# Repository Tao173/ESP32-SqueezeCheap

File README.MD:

This was my first attempt at making a cheap squeeze client for multi room audio using 
https://github.com/sle118/squeezelite-esp32
I used the ESP32-A1S to avoid having to solder too many SMD parts. 
This was a mistake as the A1S is a massive pain to work with. 
This board also has a fair amount of digital noise and I'm too inexperienced to determine if its the board design or the A1S. 

I suggest you do not use this version and use my next revision.

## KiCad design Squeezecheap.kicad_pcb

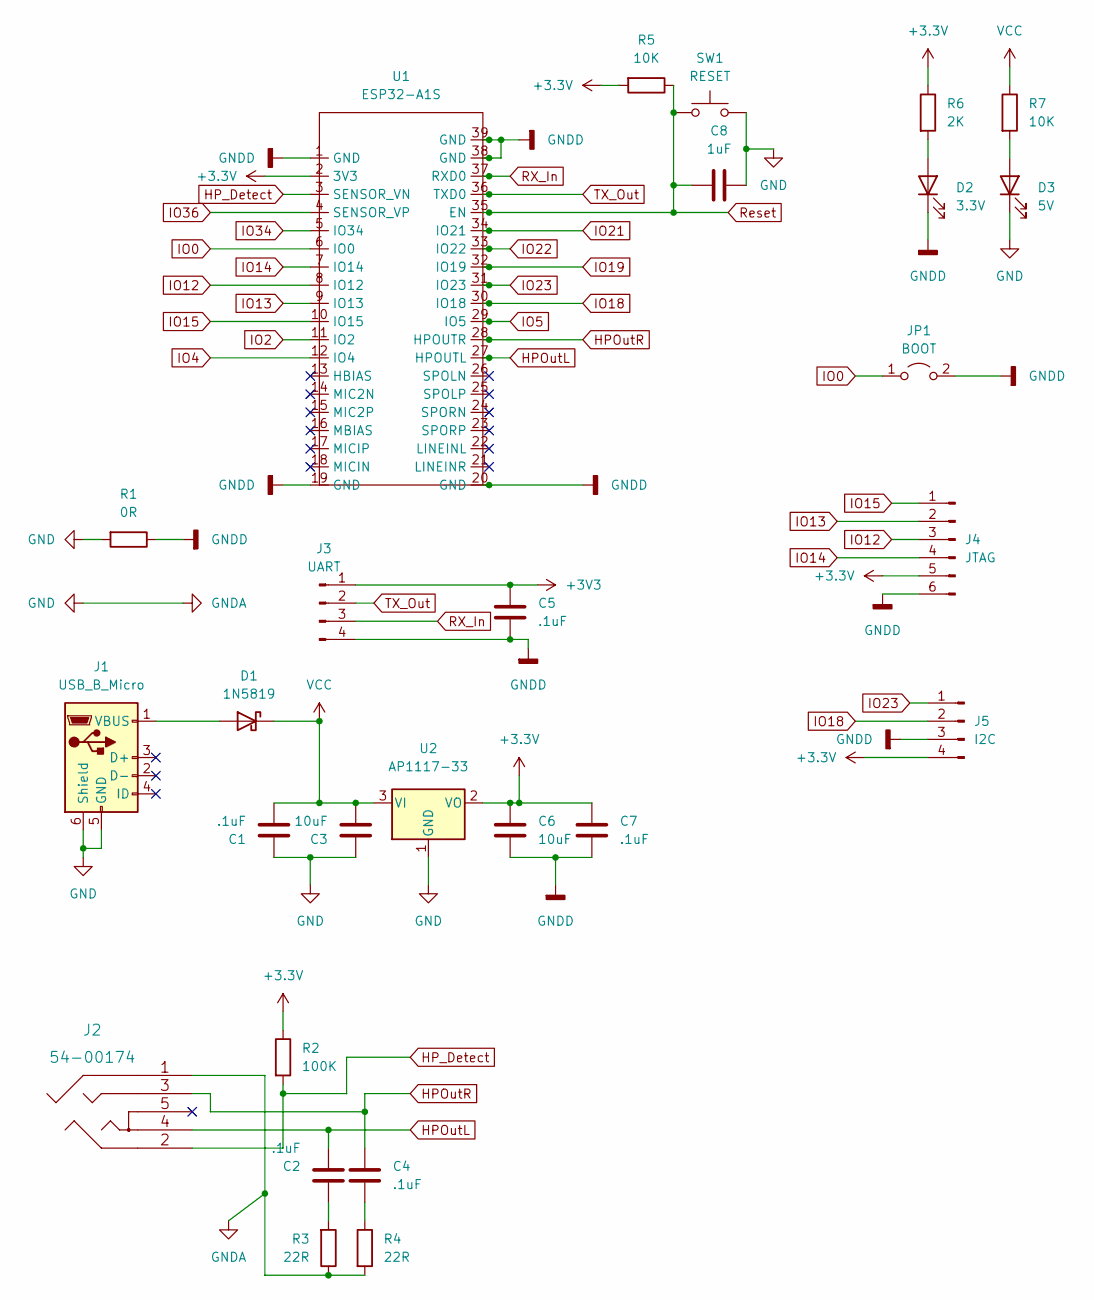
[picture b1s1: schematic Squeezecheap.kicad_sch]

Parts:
C1, C2, C4, C5, C7: .1uF; C_0805_2012Metric_Pad1.18x1.45mm_HandSolder
C3, C6: 10uF; C_0805_2012Metric_Pad1.18x1.45mm_HandSolder
C8: 1uF; C_0805_2012Metric_Pad1.18x1.45mm_HandSolder
D1: 1N5819; D_0805_2012Metric_Pad1.15x1.40mm_HandSolder
D2: 3.3V; LED_0805_2012Metric_Pad1.15x1.40mm_HandSolder
D3: 5V; LED_0805_2012Metric_Pad1.15x1.40mm_HandSolder
J1: USB_B_Micro; USB_Micro-B_Amphenol_10118194_Horizontal
J2: 54-00174
J3: UART; PinHeader_1x04_P2.54mm_Vertical
J4: JTAG; PinHeader_1x06_P2.54mm_Vertical
J5: I2C; PinHeader_1x04_P2.54mm_Vertical
JP1: BOOT; SolderJumper-2_P1.3mm_Open_Pad1.0x1.5mm
R1: 0R; R_0805_2012Metric_Pad1.20x1.40mm_HandSolder
R2: 100K; R_0805_2012Metric_Pad1.20x1.40mm_HandSolder
R3, R4: 22R; R_0805_2012Metric_Pad1.20x1.40mm_HandSolder
R5, R7: 10K; R_0805_2012Metric_Pad1.20x1.40mm_HandSolder
R6: 2K; R_0805_2012Metric_Pad1.20x1.40mm_HandSolder
SW1: RESET; SW_SPST_B3U-1000P
U1: ESP32-A1S
U2: AP1117-33; SOT-223-3_TabPin2

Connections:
GND: C1.1, C3.1, C8.1, D3.1 (K), J1.5 (GND), J1.6 (Shield), J2.1, R1.2, R3.1, R4.2, SW1.2, U2.1 (GND)
GNDD: C5.2, C6.2, C7.2, D2.1 (K), J3.4, J4.6, J5.3, JP1.2 (B), R1.1, U1.1 (GND), U1.19 (GND), U1.20 (GND), U1.38 (GND), U1.39 (GND)
HPOutL: C2.2, J2.4, U1.27 (HPOUTL)
HPOutR: C4.1, J2.3, U1.28 (HPOUTR)
HP_Detect: J2.2, R2.2, U1.3 (SENSOR_VN)
IO0: JP1.1 (A), U1.6 (IO0)
IO2: U1.11 (IO2)
IO4: U1.12 (IO4)
IO5: U1.29 (IO5)
IO12: J4.3, U1.8 (IO12)
IO13: J4.2, U1.9 (IO13)
IO14: J4.4, U1.7 (IO14)
IO15: J4.1, U1.10 (IO15)
IO18: J5.2, U1.30 (IO18)
IO19: U1.32 (IO19)
IO21: U1.34 (IO21)
IO22: U1.33 (IO22)
IO23: J5.1, U1.31 (IO23)
IO34: U1.5 (IO34)
IO36: U1.4 (SENSOR_VP)
unnamed: C2.1, R3.2
unnamed: C4.2, R4.1
unnamed: D1.2 (A), J1.1 (VBUS)
unnamed: D2.2 (A), R6.2
unnamed: D3.2 (A), R7.2
RX_In: J3.3, U1.37 (RXD0)
Reset: C8.2, R5.1, SW1.1, U1.35 (EN)
TX_Out: J3.2, U1.36 (TXD0)
VCC: C1.2, C3.2, D1.1 (K), R7.1, U2.3 (VI)

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
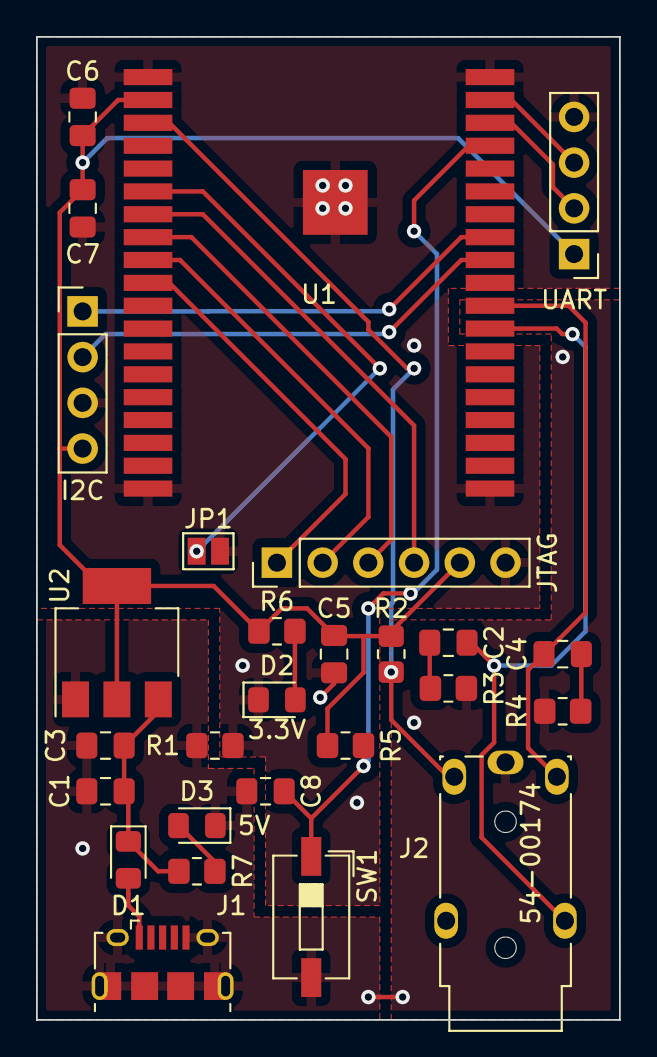
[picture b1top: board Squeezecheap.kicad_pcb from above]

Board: 2 copper layers, 32.4 x 54.6 mm, 27 parts (0 on the bottom side), 22 nets.

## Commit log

2022-04-03 Initial
    Comitting and scrapping after assembly and test lol
2022-04-03 Cleanup for redesign
